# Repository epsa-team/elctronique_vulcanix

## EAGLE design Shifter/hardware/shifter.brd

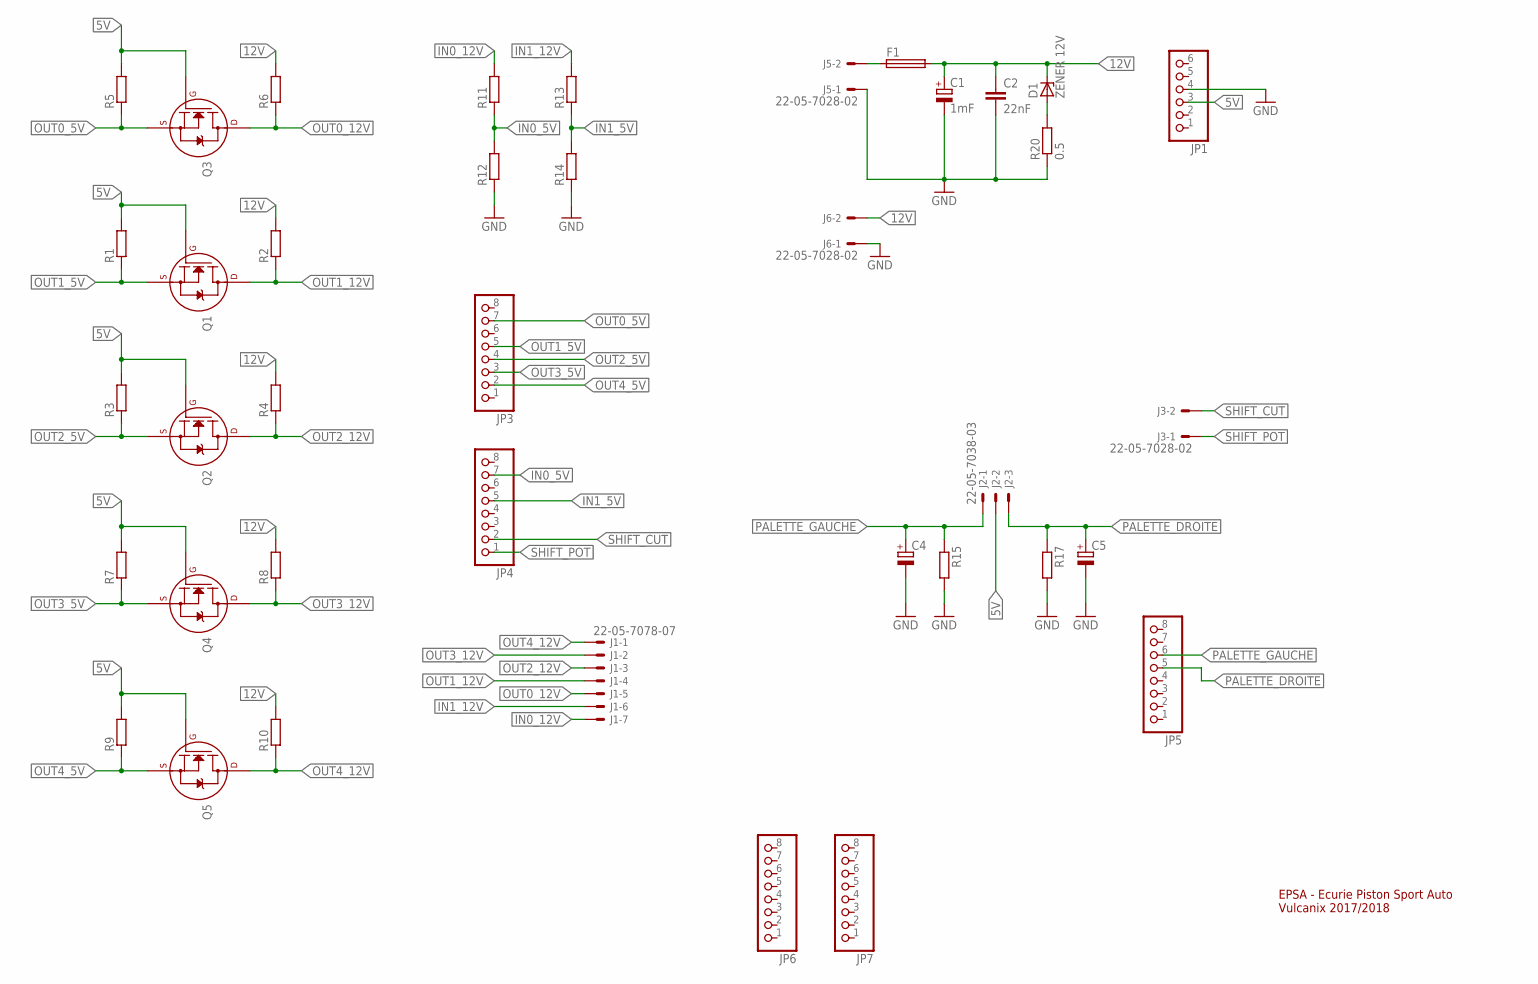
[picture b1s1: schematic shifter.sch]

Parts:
C1: 1mF; E7,5-16
C2: 22nF; C025-025X050
C4, C5: CPOL-EUE2,5-6E; E2,5-6E
D1: ZENER 12V; DO41Z10
F1: SH25
J1: 22-05-7078-07; 7395-07
J2: 22-05-7038-03; 7395-03
J3, J5, J6: 22-05-7028-02; 7395-02
JP1: HEADER-1X6; 1X06_OVAL
JP3, JP4: HEADER-1X8; 1X08_OVAL
JP5, JP6, JP7: PINHD-1X8; 1X08
Q1, Q2, Q3, Q4, Q5: 2N7000_TO92; TO-92
R1, R2, R3, R4, R5, R6, R7, R8, R9, R10, R11, R12, R13, R14, R15, R17: R-EU_0204/7; 0204/7
R20: 0.5; 0309/12

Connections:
5V: J2.2, JP1.3, Q1.2 (G), Q2.2 (G), Q3.2 (G), Q4.2 (G), Q5.2 (G), R1.2, R3.2, R5.2, R7.2, R9.2
12V: C1.+, C2.1, D1.C, F1.2, J6.2, R2.2, R4.2, R6.2, R8.2, R10.2
GND: C1.-, C2.2, C4.-, C5.-, J5.1, J6.1, JP1.4, R12.1, R14.1, R15.2, R17.2, R20.1
IN0_5V: JP4.7, R11.1, R12.2
IN0_12V: J1.7, R11.2
IN1_5V: JP4.5, R13.1, R14.2
IN1_12V: J1.6, R13.2
unnamed: F1.1, J5.2
unnamed: D1.A, R20.2
OUT0_5V: JP3.7, Q3.1 (S), R5.1
OUT0_12V: J1.5, Q3.3 (D), R6.1
OUT1_5V: JP3.5, Q1.1 (S), R1.1
OUT1_12V: J1.4, Q1.3 (D), R2.1
OUT2_5V: JP3.4, Q2.1 (S), R3.1
OUT2_12V: J1.3, Q2.3 (D), R4.1
OUT3_5V: JP3.3, Q4.1 (S), R7.1
OUT3_12V: J1.2, Q4.3 (D), R8.1
OUT4_5V: JP3.2, Q5.1 (S), R9.1
OUT4_12V: J1.1, Q5.3 (D), R10.1
PALETTE_DROITE: C5.+, J2.3, JP5.5, R17.1
PALETTE_GAUCHE: C4.+, J2.1, JP5.6, R15.1
SHIFT_CUT: J3.2, JP4.2
SHIFT_POT: J3.1, JP4.1

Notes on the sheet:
EPSA - Ecurie Piston Sport Auto Vulcanix 2017/2018

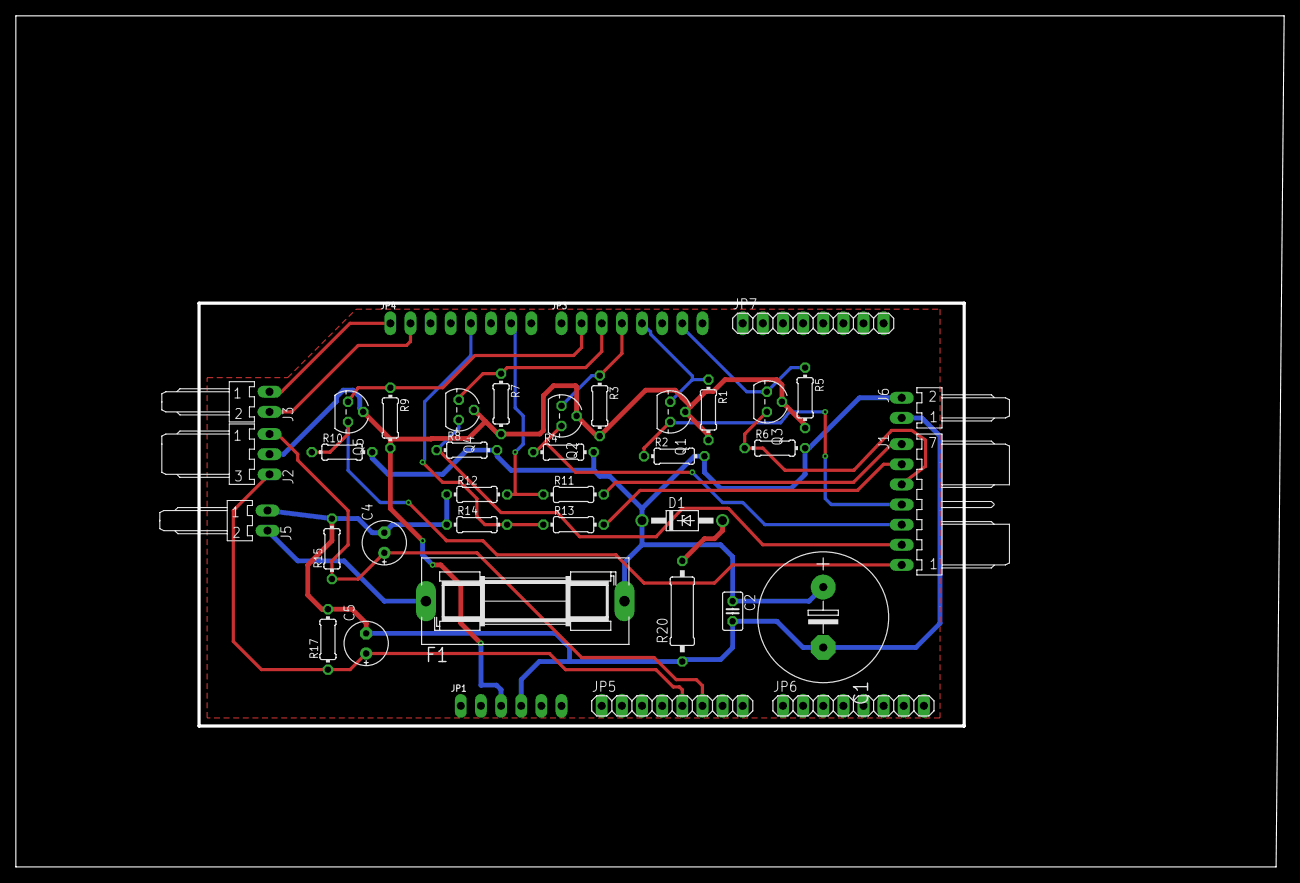
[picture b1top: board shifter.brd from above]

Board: 2 copper layers, 160.0 x 107.4 mm, 39 parts (0 on the bottom side), 23 nets.

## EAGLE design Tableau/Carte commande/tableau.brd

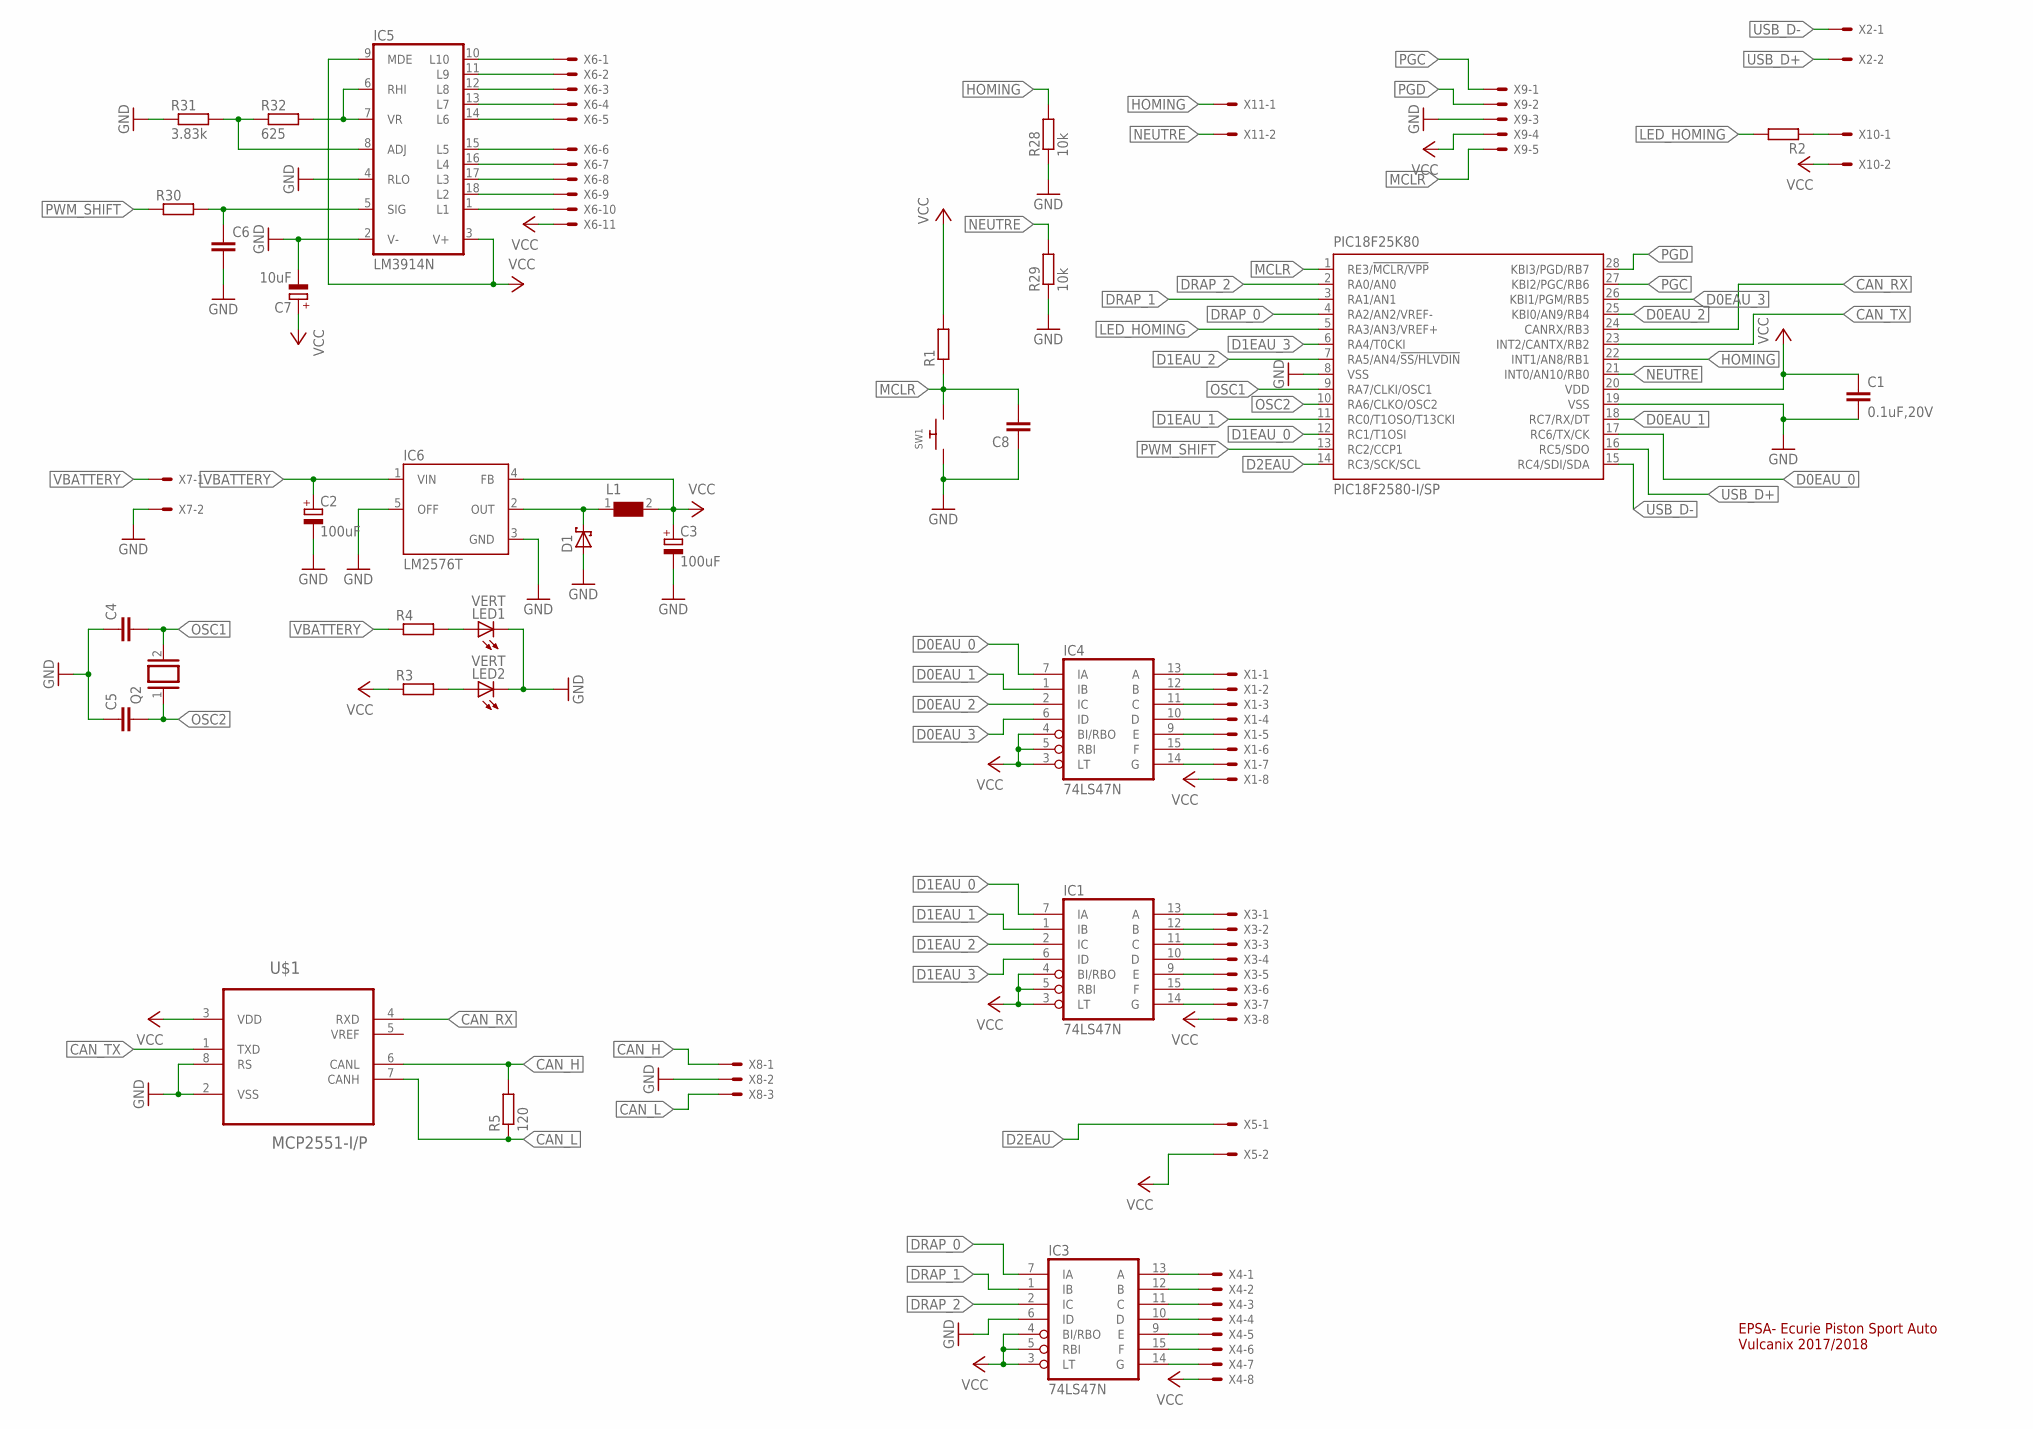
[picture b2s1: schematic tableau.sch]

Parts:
C1: 0.1uF,20V; C025-025X050
C2, C3: 100uF; E2-5
C4, C5, C8: C-EU025-030X050; C025-030X050
C6: C-EU025-025X050; C025-025X050
C7: 10uF; E2-5
D1: SCHOTTKY-DIODEDO201T15; DO201T15
IC1, IC3, IC4: 74LS47N; DIL16
IC5: LM3914N; DIL18
IC6: LM2576T; TO220-5
L1: WE-TI-744743102_8012B; WE-TI_8012B
LED1, LED2: VERT; LED3MM
PIC18F25K80: PIC18F2580-I/SP; DIL28-3
Q2: XTAL/S; QS
R1, R2, R3, R4, R30: R-EU_0204/7; 0204/7
R5: 120; 0204/7
R28, R29: 10k; 0204/7
R31: 3.83k; 0204/7
R32: 625; 0204/7
SW1: SWITCH_PUSHBUTTONSOFTTOUCHSMD_SJ; PUSHBUTTON_SMD_SJ
U$1: MCP2551-I/P; DIP254P762X432-8
X1, X3, X4: KK-156-8
X2, X5, X7, X10, X11: KK-156-2
X6: KK-156-11
X8: KK-156-3
X9: KK-156-5

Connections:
CAN_H: R5.2, U$1.6 (CANL), X8.1
CAN_L: R5.1, U$1.7 (CANH), X8.3
CAN_RX: PIC18F25K80.24 (CANRX/RB3), U$1.4 (RXD)
CAN_TX: PIC18F25K80.23 (INT2/CANTX/RB2), U$1.1 (TXD)
D0EAU_0: IC4.7 (IA), PIC18F25K80.17 (RC6/TX/CK)
D0EAU_1: IC4.1 (IB), PIC18F25K80.18 (RC7/RX/DT)
D0EAU_2: IC4.2 (IC), PIC18F25K80.25 (KBI0/AN9/RB4)
D0EAU_3: IC4.6 (ID), PIC18F25K80.26 (KBI1/PGM/RB5)
D1EAU_0: IC1.7 (IA), PIC18F25K80.12 (RC1/T1OSI)
D1EAU_1: IC1.1 (IB), PIC18F25K80.11 (RC0/T1OSO/T13CKI)
D1EAU_2: IC1.2 (IC), PIC18F25K80.7 (RA5/AN4/!SS/HLVDIN)
D1EAU_3: IC1.6 (ID), PIC18F25K80.6 (RA4/T0CKI)
D2EAU: PIC18F25K80.14 (RC3/SCK/SCL), X5.1
DRAP_0: IC3.7 (IA), PIC18F25K80.4 (RA2/AN2/VREF-)
DRAP_1: IC3.1 (IB), PIC18F25K80.3 (RA1/AN1)
DRAP_2: IC3.2 (IC), PIC18F25K80.2 (RA0/AN0)
GND: C1.2, C2.-, C3.-, C4.1, C5.1, C6.2, C7.-, C8.1, D1.A, IC1.8 (GND), IC3.6 (ID), IC3.8 (GND), IC4.8 (GND), IC5.2 (V-), IC5.4 (RLO), IC6.3 (GND), IC6.5 (OFF), LED1.K (C), LED2.K (C), PIC18F25K80.8 (VSS), PIC18F25K80.19 (VSS), R28.1, R29.1, R31.1, SW1.P$1, U$1.2 (VSS), U$1.8 (RS), X7.2, X8.2, X9.3
HOMING: PIC18F25K80.22 (INT1/AN8/RB1), R28.2, X11.1
LED_HOMING: PIC18F25K80.5 (RA3/AN3/VREF+), R2.2
MCLR: C8.2, PIC18F25K80.1 (RE3/!MCLR/VPP), R1.1, SW1.P$2, X9.5
unnamed: LED1.A, R4.2
unnamed: IC4.13 (A), X1.1
unnamed: LED2.A, R3.2
unnamed: R2.1, X10.1
unnamed: IC4.12 (B), X1.2
unnamed: IC4.11 (C), X1.3
unnamed: IC4.10 (D), X1.4
unnamed: IC4.9 (E), X1.5
unnamed: IC4.15 (F), X1.6
unnamed: IC4.14 (G), X1.7
unnamed: IC1.13 (A), X3.1
unnamed: IC1.12 (B), X3.2
unnamed: IC1.11 (C), X3.3
unnamed: IC1.10 (D), X3.4
unnamed: IC1.9 (E), X3.5
unnamed: IC1.15 (F), X3.6
unnamed: IC1.14 (G), X3.7
unnamed: IC3.13 (A), X4.1
unnamed: IC3.12 (B), X4.2
unnamed: IC3.11 (C), X4.3
unnamed: IC3.10 (D), X4.4
unnamed: IC3.9 (E), X4.5
unnamed: IC3.15 (F), X4.6
unnamed: IC3.14 (G), X4.7
unnamed: IC5.10 (L10), X6.1
unnamed: IC5.11 (L9), X6.2
unnamed: IC5.12 (L8), X6.3
unnamed: IC5.13 (L7), X6.4
unnamed: IC5.14 (L6), X6.5
unnamed: IC5.15 (L5), X6.6
unnamed: IC5.16 (L4), X6.7
unnamed: IC5.17 (L3), X6.8
unnamed: IC5.18 (L2), X6.9
unnamed: IC5.1 (L1), X6.10
unnamed: C6.1, IC5.5 (SIG), R30.2
unnamed: IC5.6 (RHI), IC5.7 (VR), R32.2
unnamed: IC5.8 (ADJ), R31.2, R32.1
unnamed: D1.C, IC6.2 (OUT), L1.1
NEUTRE: PIC18F25K80.21 (INT0/AN10/RB0), R29.2, X11.2
OSC1: C4.2, PIC18F25K80.9 (RA7/CLKI/OSC1), Q2.2
OSC2: C5.2, PIC18F25K80.10 (RA6/CLKO/OSC2), Q2.1
PGC: PIC18F25K80.27 (KBI2/PGC/RB6), X9.1
PGD: PIC18F25K80.28 (KBI3/PGD/RB7), X9.2
PWM_SHIFT: PIC18F25K80.13 (RC2/CCP1), R30.1
USB_D+: PIC18F25K80.16 (RC5/SDO), X2.2
USB_D-: PIC18F25K80.15 (RC4/SDI/SDA), X2.1
VBATTERY: C2.+, IC6.1 (VIN), R4.1, X7.1
VCC: C1.1, C3.+, C7.+, IC1.3 (LT), IC1.4 (BI/RBO), IC1.5 (RBI), IC1.16 (VCC), IC3.3 (LT), IC3.4 (BI/RBO), IC3.5 (RBI), IC3.16 (VCC), IC4.3 (LT), IC4.4 (BI/RBO), IC4.5 (RBI), IC4.16 (VCC), IC5.3 (V+), IC5.9 (MDE), IC6.4 (FB), L1.2, PIC18F25K80.20 (VDD), R1.2, R3.1, U$1.3 (VDD), X1.8, X3.8, X4.8, X5.2, X6.11, X9.4, X10.2

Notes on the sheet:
EPSA- Ecurie Piston Sport Auto Vulcanix 2017/2018

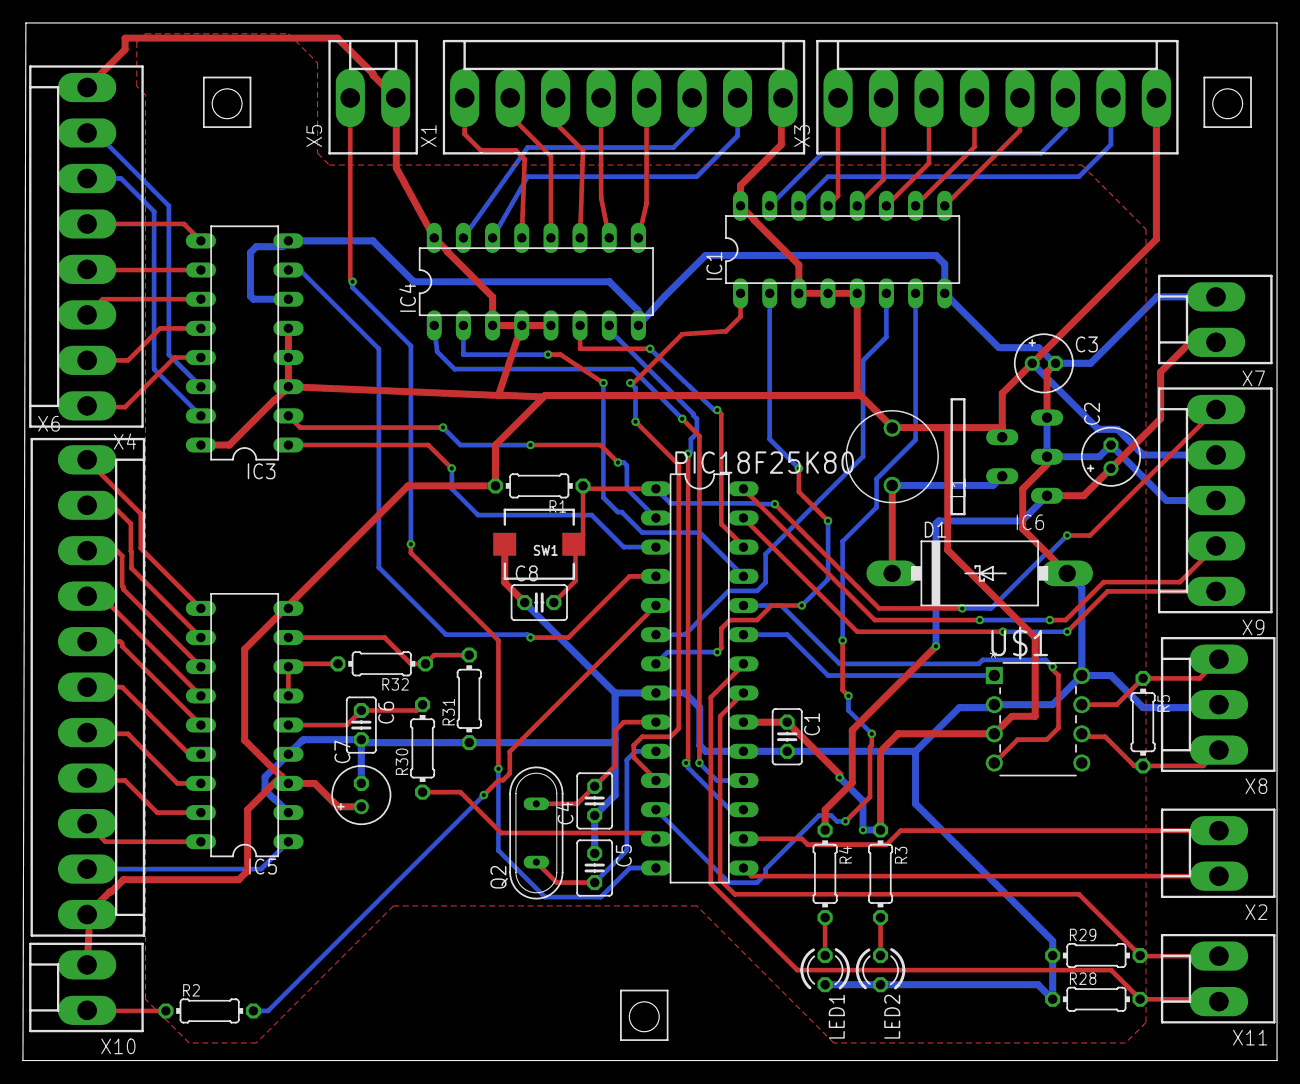
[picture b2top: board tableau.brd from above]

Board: 2 copper layers, 109.2 x 90.3 mm, 42 parts (0 on the bottom side), 68 nets.

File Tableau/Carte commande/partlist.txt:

Partlist

Exported from tableau.sch at 02-Jan-18 10:25 PM

EAGLE Version 8.4.3 Copyright (c) 1988-2017 Autodesk, Inc.

Assembly variant: 

Part        Value           Device                           Package           Library      Sheet

C1          0.1uF,20V       C-EU025-025X050                  C025-025X050      rcl          1
C2          100uF           CPOL-EUE2-5                      E2-5              rcl          1
C3          100uF           CPOL-EUE2-5                      E2-5              rcl          1
C4                          C-EU025-030X050                  C025-030X050      rcl          1
C5                          C-EU025-030X050                  C025-030X050      rcl          1
C6                          C-EU025-025X050                  C025-025X050      resistor     1
C7          10uF            CPOL-EUE2-5                      E2-5              rcl          1
C8                          C-EU025-030X050                  C025-030X050      rcl          1
D1                          SCHOTTKY-DIODEDO201T15           DO201T15          diode        1
IC1         74LS47N         74LS47N                          DIL16             74xx-eu      1
IC3         74LS47N         74LS47N                          DIL16             74xx-eu      1
IC4         74LS47N         74LS47N                          DIL16             74xx-eu      1
IC5         LM3914N         LM3914N                          DIL18             linear       1
IC6         LM2576T         LM2576T                          TO220-5           v-reg-3      1
L1                          WE-TI-744743102_8012B            WE-TI_8012B       WE-TI        1
LED1        VERT            LED3MM                           LED3MM            led          1
LED2        VERT            LED3MM                           LED3MM            led          1
PIC18F25K80 PIC18F2580-I/SP PIC18F2580-I/SP                  DIL28-3           microchip    1
Q2                          XTAL/S                           QS                special      1
R1                          R-EU_0204/7                      0204/7            resistor     1
R2                          R-EU_0204/7                      0204/7            resistor     1
R3                          R-EU_0204/7                      0204/7            resistor     1
R4                          R-EU_0204/7                      0204/7            resistor     1
R5          120             R-EU_0204/7                      0204/7            resistor     1
R28                         R-EU_0204/7                      0204/7            resistor     1
R29                         R-EU_0204/7                      0204/7            resistor     1
R30                         R-EU_0204/7                      0204/7            resistor     1
R31         3.83k           R-EU_0204/7                      0204/7            resistor     1
R32         625             R-EU_0204/7                      0204/7            resistor     1
SW1                         SWITCH_PUSHBUTTONSOFTTOUCHSMD_SJ PUSHBUTTON_SMD_SJ microbuilder 1
U$1         MCP2551-I/P     MCP2551-I/P                      DIP254P762X432-8  mcp2551      1
X1                          KK-156-8                         KK-156-8          con-molex    1
X2                          KK-156-2                         KK-156-2          con-molex    1
X3                          KK-156-8                         KK-156-8          con-molex    1
X4                          KK-156-8                         KK-156-8          con-molex    1
X5                          KK-156-2                         KK-156-2          con-molex    1
X6                          KK-156-11                        KK-156-11         con-molex    1
X7                          KK-156-2                         KK-156-2          con-molex    1
X8                          KK-156-3                         KK-156-3          con-molex    1
X9                          KK-156-5                         KK-156-5          con-molex    1
X10                         KK-156-2                         KK-156-2          con-molex    1
X11                         KK-156-2                         KK-156-2          con-molex    1

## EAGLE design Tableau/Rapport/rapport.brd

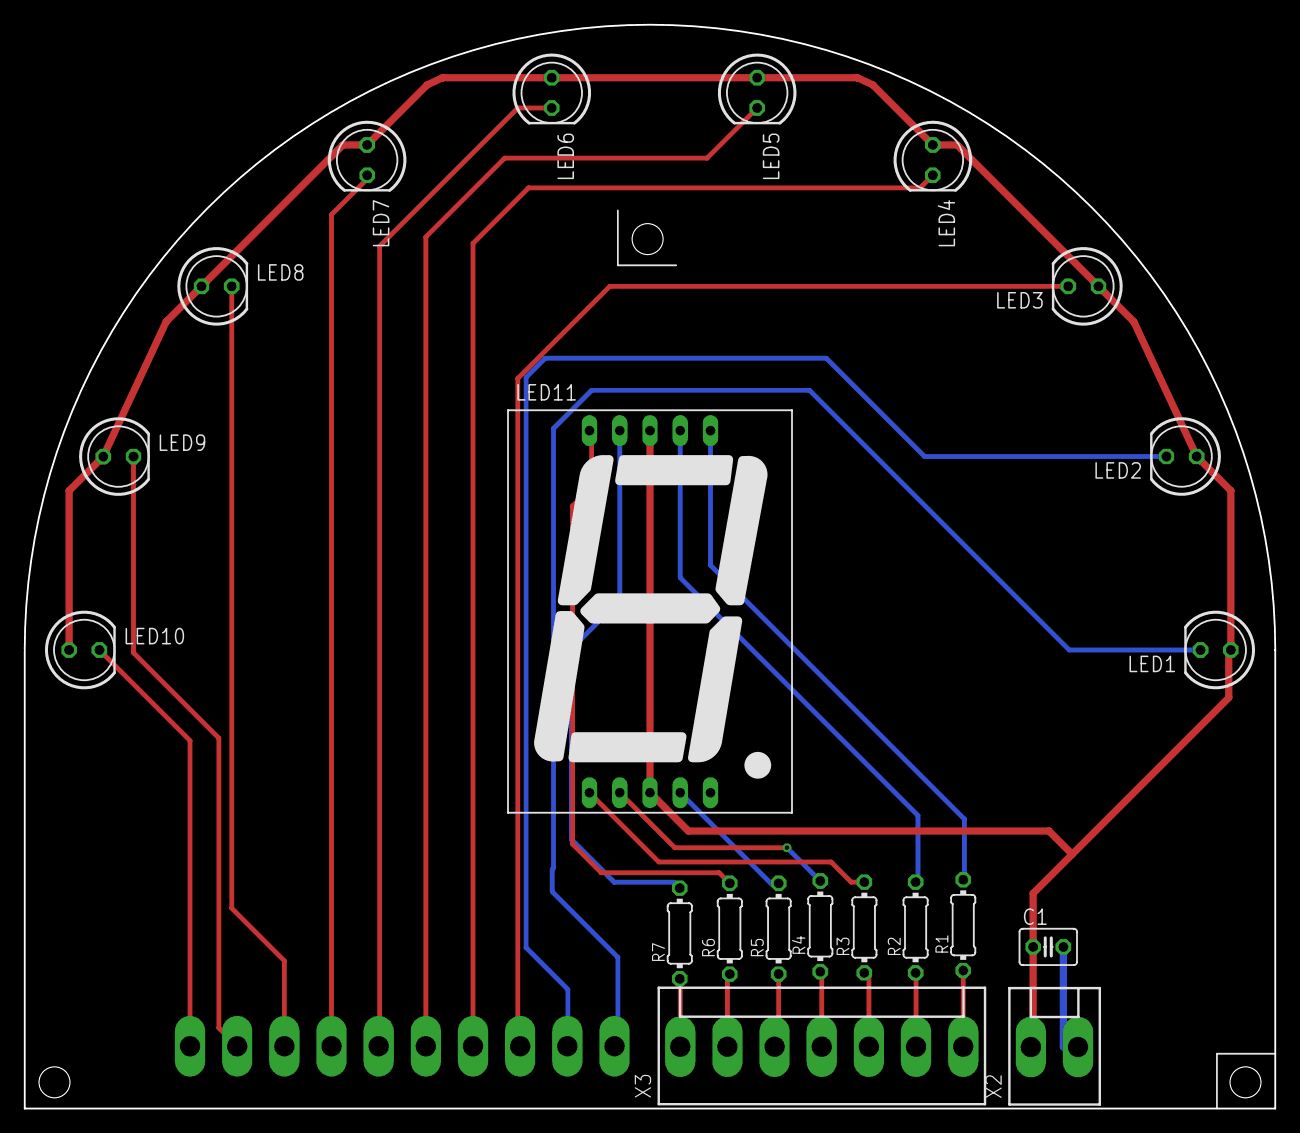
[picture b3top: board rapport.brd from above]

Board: 2 copper layers, 105.0 x 91.0 mm, 22 parts (1 on the bottom side), 26 nets.

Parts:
C1: C025-030X050
LED1, LED2, LED3, LED4, LED5, LED6, LED7, LED8, LED9, LED10: LED5MM
LED11: 7-SEG_SA10-21; SA10-21
R1, R2, R3, R4, R5, R6, R7: 0204/7
X1: KK-156-10
X2: KK-156-2
X3: KK-156-7

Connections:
7SEG_A: R7.1, X3.1
7SEG_B: R6.1, X3.2
7SEG_C: R5.1, X3.3
7SEG_D: R4.1, X3.4
7SEG_E: R3.1, X3.5
7SEG_F: R2.1, X3.6
7SEG_G: R1.1, X3.7
BARGRAPH_0: LED1.K, X1.1
BARGRAPH_1: LED2.K, X1.2
BARGRAPH_2: LED3.K, X1.3
BARGRAPH_3: LED4.K, X1.4
BARGRAPH_4: LED5.K, X1.5
BARGRAPH_5: LED6.K, X1.6
BARGRAPH_6: LED7.K, X1.7
BARGRAPH_7: LED8.K, X1.8
BARGRAPH_8: LED9.K, X1.9
BARGRAPH_9: LED10.K, X1.10
GND: C1.2, X2.2
unnamed: LED11.7, R7.2
unnamed: LED11.6, R6.2
unnamed: LED11.4, R5.2
unnamed: LED11.2, R4.2
unnamed: LED11.1, R3.2
unnamed: LED11.9, R2.2
unnamed: LED11.10, R1.2
VCC: C1.1, LED1.A, LED2.A, LED3.A, LED4.A, LED5.A, LED6.A, LED7.A, LED8.A, LED9.A, LED10.A, LED11.3, LED11.8, X2.1

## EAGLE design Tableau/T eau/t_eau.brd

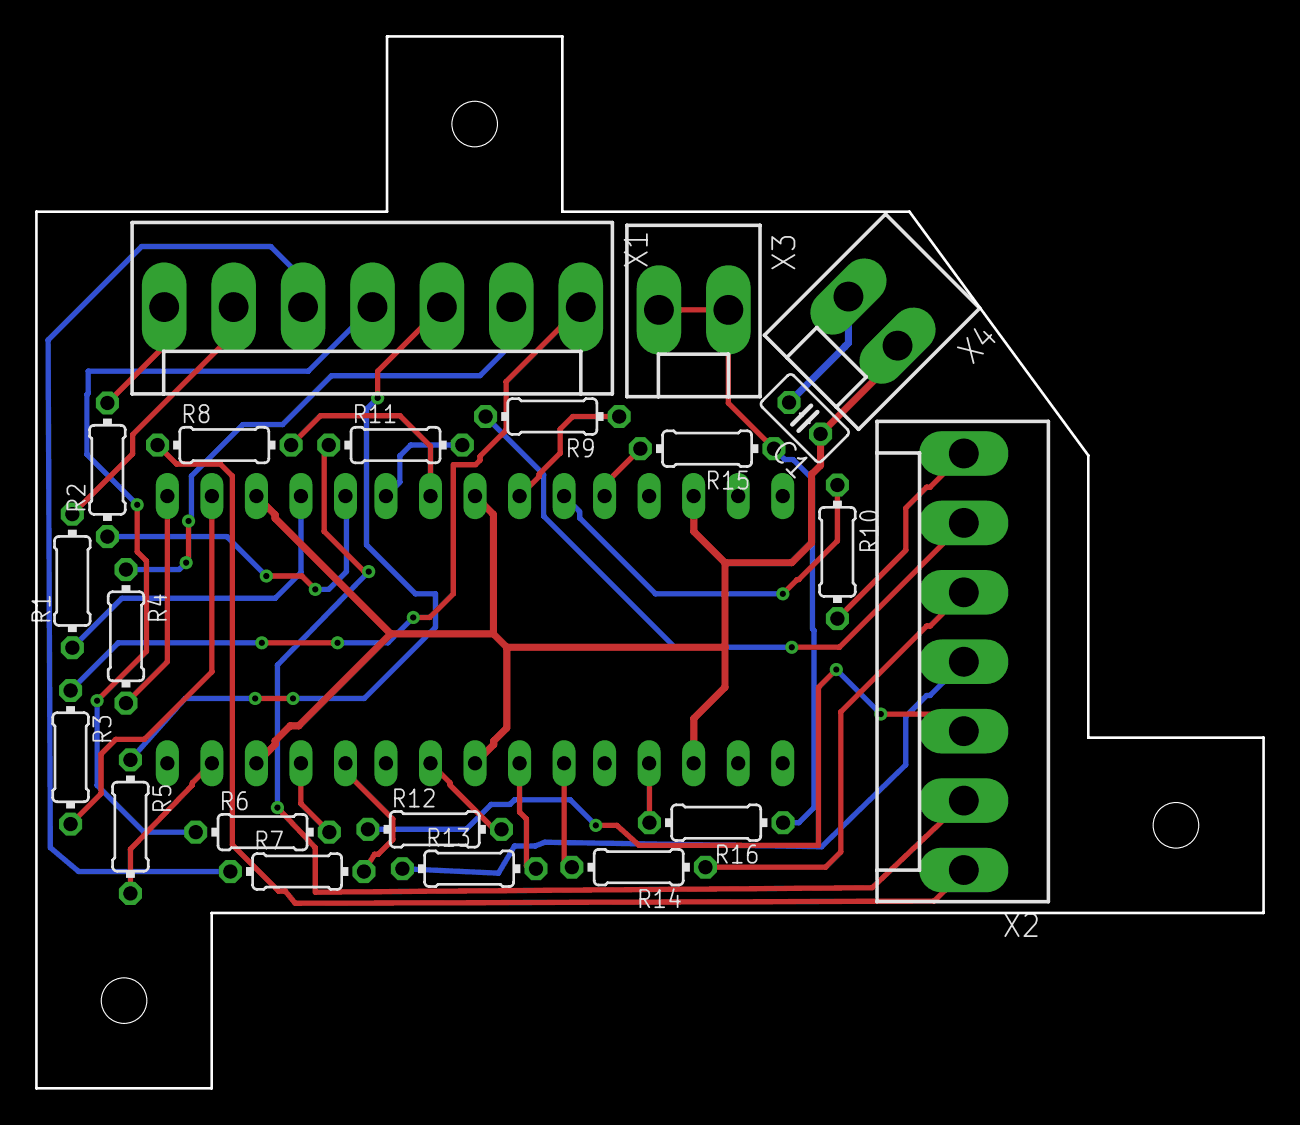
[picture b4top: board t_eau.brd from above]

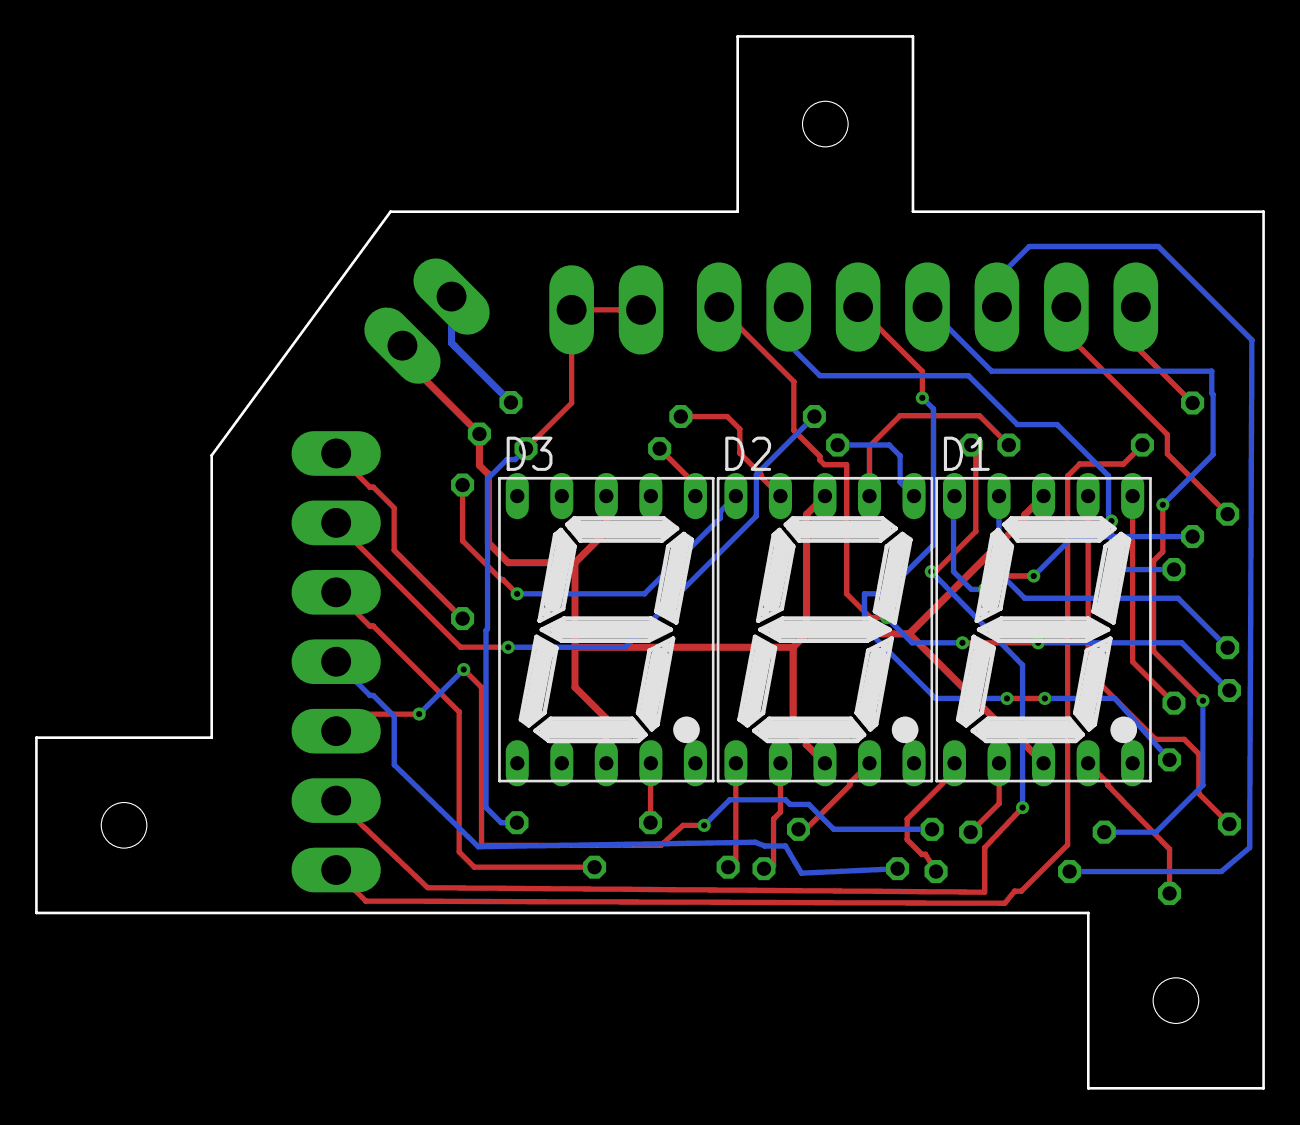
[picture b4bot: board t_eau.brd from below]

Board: 2 copper layers, 70.0 x 60.0 mm, 24 parts (3 on the bottom side), 33 nets.

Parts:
C1: C025-025X050
D1, D2, D3: 7SEG-13
R1, R2, R3, R4, R5, R6, R7, R8, R9, R10, R11, R12, R13, R14, R15, R16: 0204/7
X1, X2: KK-156-7
X3, X4: KK-156-2

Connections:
D1_A: R3.1, X1.1
D1_B: R4.1, X1.2
D1_C: R5.1, X1.3
D1_D: R6.1, X1.4
D1_E: R7.1, X1.5
D1_F: R1.2, X1.6
D1_G: R2.2, X1.7
D2_A: R8.1, X2.1
D2_B: R11.1, X2.2
D2_C: R12.1, X2.3
D2_D: R13.1, X2.4
D2_E: R14.1, X2.5
D2_F: R9.2, X2.6
D2_G: R10.2, X2.7
D3: R15.1, R16.1, X3.1, X3.2
GND: C1.2, X4.2
unnamed: D1.7, R3.2
unnamed: D1.6, R4.2
unnamed: D1.4, R5.2
unnamed: D1.2, R6.2
unnamed: D1.1, R7.2
unnamed: D1.9, R1.1
unnamed: D1.10, R2.1
unnamed: D2.7, R8.2
unnamed: D2.6, R11.2
unnamed: D2.4, R12.2
unnamed: D2.2, R13.2
unnamed: D2.1, R14.2
unnamed: D2.9, R9.1
unnamed: D2.10, R10.1
unnamed: D3.4, R16.2
unnamed: D3.6, R15.2
VCC: C1.1, D1.3, D1.8, D2.3, D2.8, D3.3, D3.8, X4.1

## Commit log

2018-01-16 no message
2018-02-17 modif t_eau

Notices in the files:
parts and their libraries:
microbuilder: This work is placed in the public domain, and may be freely used for commercial and non-commercial work with the following conditions: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
